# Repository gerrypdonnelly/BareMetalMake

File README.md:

# BareMetalMake
Folder to contain baremetal programming of microcontrollers

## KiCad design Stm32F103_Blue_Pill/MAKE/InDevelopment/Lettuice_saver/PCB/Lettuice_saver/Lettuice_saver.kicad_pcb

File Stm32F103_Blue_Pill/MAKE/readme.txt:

The syscalls.c was created in w3a to accomodate printf
THe linker startup and make files were modified to accomodate the printf through syscalls.c

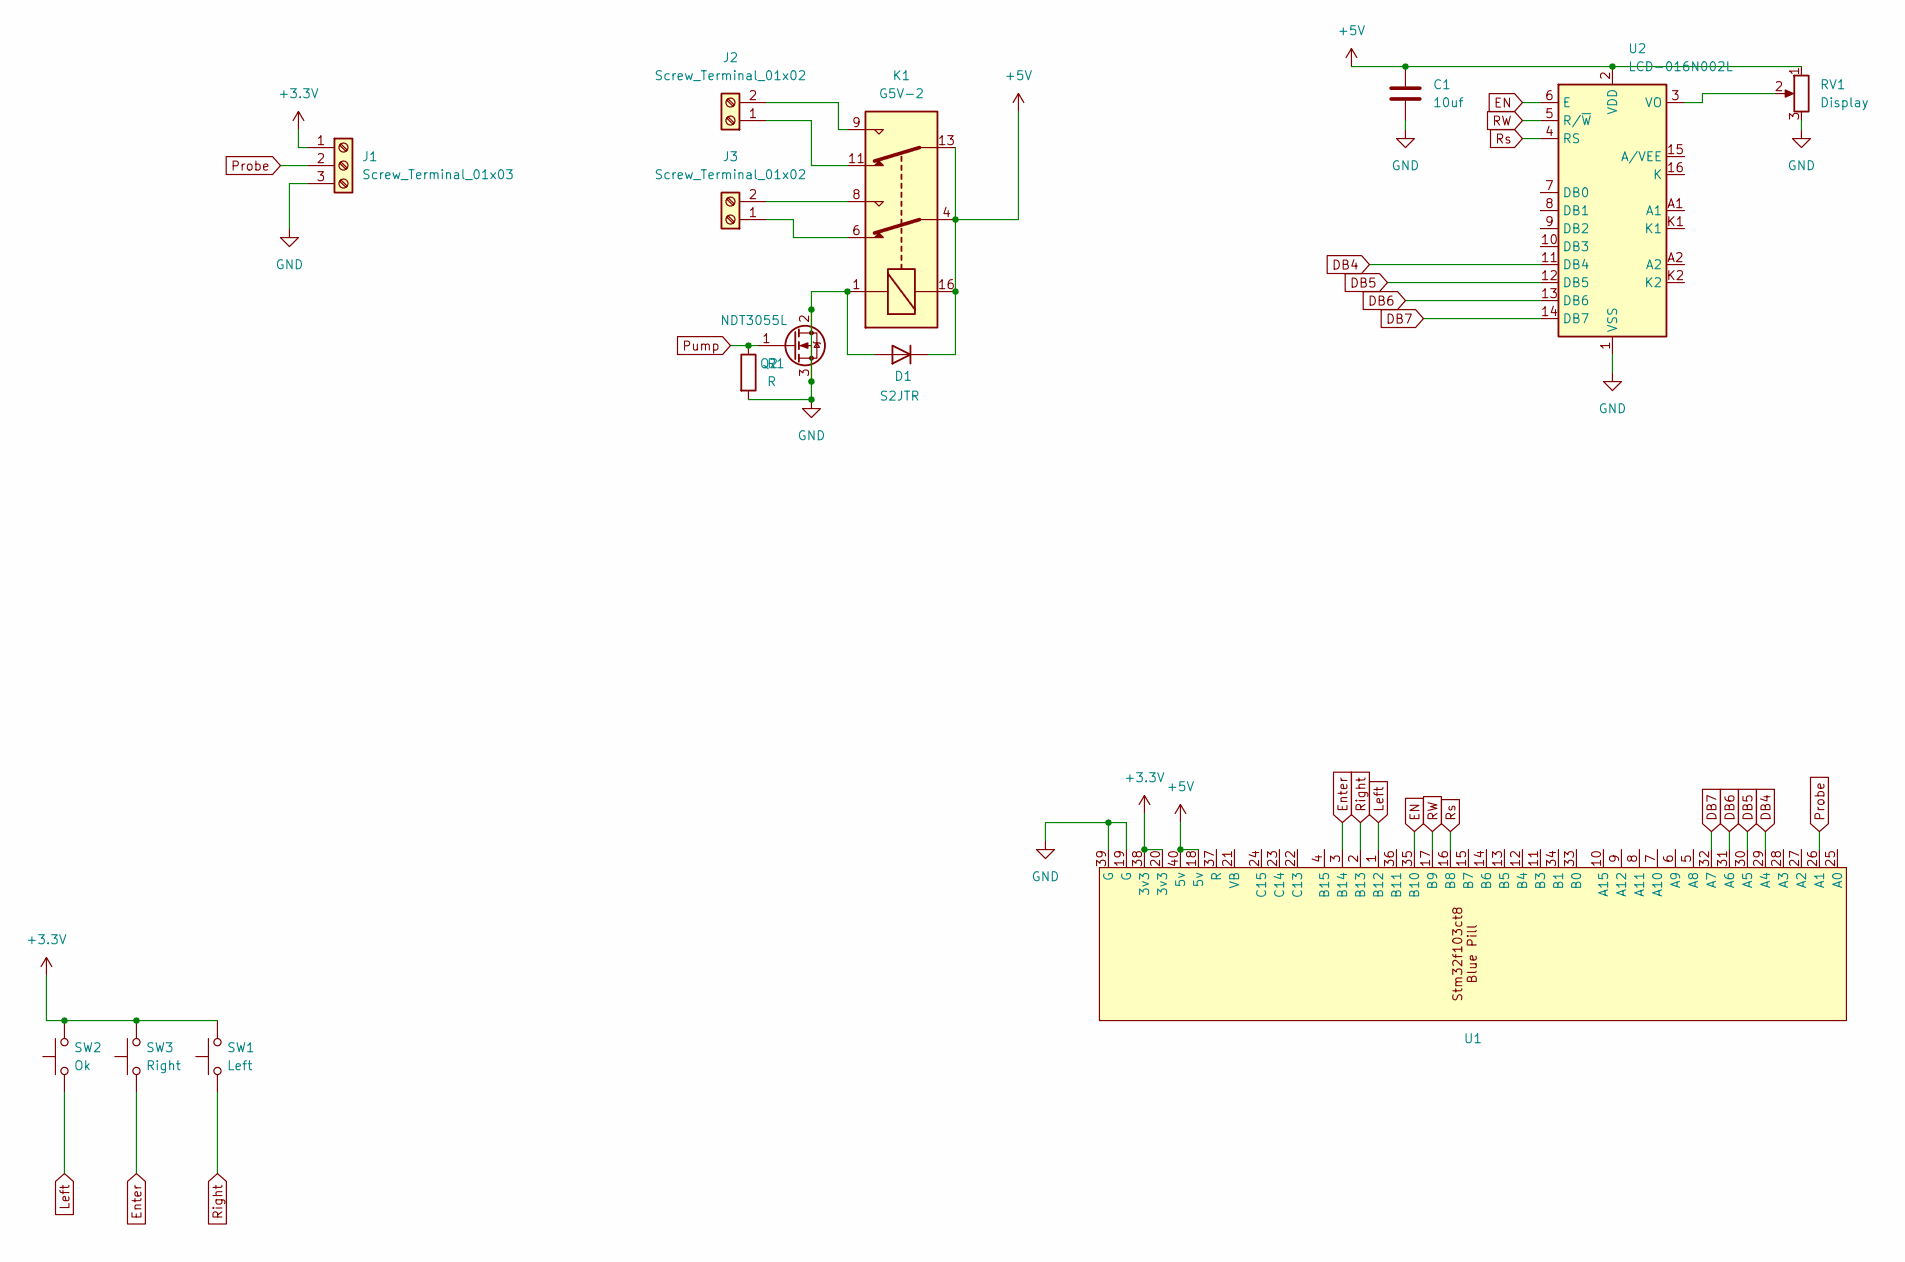
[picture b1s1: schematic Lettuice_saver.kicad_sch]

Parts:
C1: 10uf; C_0402_1005Metric
D1: S2JTR; D_SMB
J1: Screw_Terminal_01x03; TerminalBlock_MaiXu_MX126-5.0-03P_1x03_P5.00mm
J2, J3: Screw_Terminal_01x02; TerminalBlock_MaiXu_MX126-5.0-02P_1x02_P5.00mm
K1: G5V-2; Relay_DPDT_Omron_G5V-2
Q2: NDT3055L; SOT-223-3_TabPin2
R1: R; R_0402_1005Metric
RV1: Display; Potentiometer_Runtron_RM-065_Vertical
SW1: Left; SW_PUSH_6mm
SW2: Ok; SW_PUSH_6mm
SW3: Right; SW_PUSH_6mm
U1: STM32F103 Blue Pill; Blue Pill
U2: LCD-016N002L

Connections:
+3.3V: J1.1, SW1.2, SW2.2, SW3.2, U1.20 (3v3), U1.38 (3v3)
+5V: C1.1, D1.1 (K), K1.4, K1.13, K1.16, RV1.1, U1.18 (5v), U1.40 (5v), U2.2 (VDD)
DB4: U1.29 (A4), U2.11 (DB4)
DB5: U1.30 (A5), U2.12 (DB5)
DB6: U1.31 (A6), U2.13 (DB6)
DB7: U1.32 (A7), U2.14 (DB7)
EN: U1.35 (B10), U2.6 (E)
Enter: SW3.1, U1.3 (B14)
GND: C1.2, D1.2 (A), J1.3, K1.1, Q2.2 (D), Q2.3 (S), R1.2, RV1.3, U1.19 (G), U1.39 (G), U2.1 (VSS)
Left: SW2.1, U1.1 (B12)
unnamed: J2.1, K1.11
unnamed: J2.2, K1.9
unnamed: J3.1, K1.6
unnamed: J3.2, K1.8
unnamed: RV1.2, U2.3 (VO)
Probe: J1.2, U1.26 (A1)
Pump: Q2.1 (G), R1.1
RW: U1.17 (B9), U2.5 (R/~W)
Right: SW1.1, U1.2 (B13)
Rs: U1.16 (B8), U2.4 (RS)

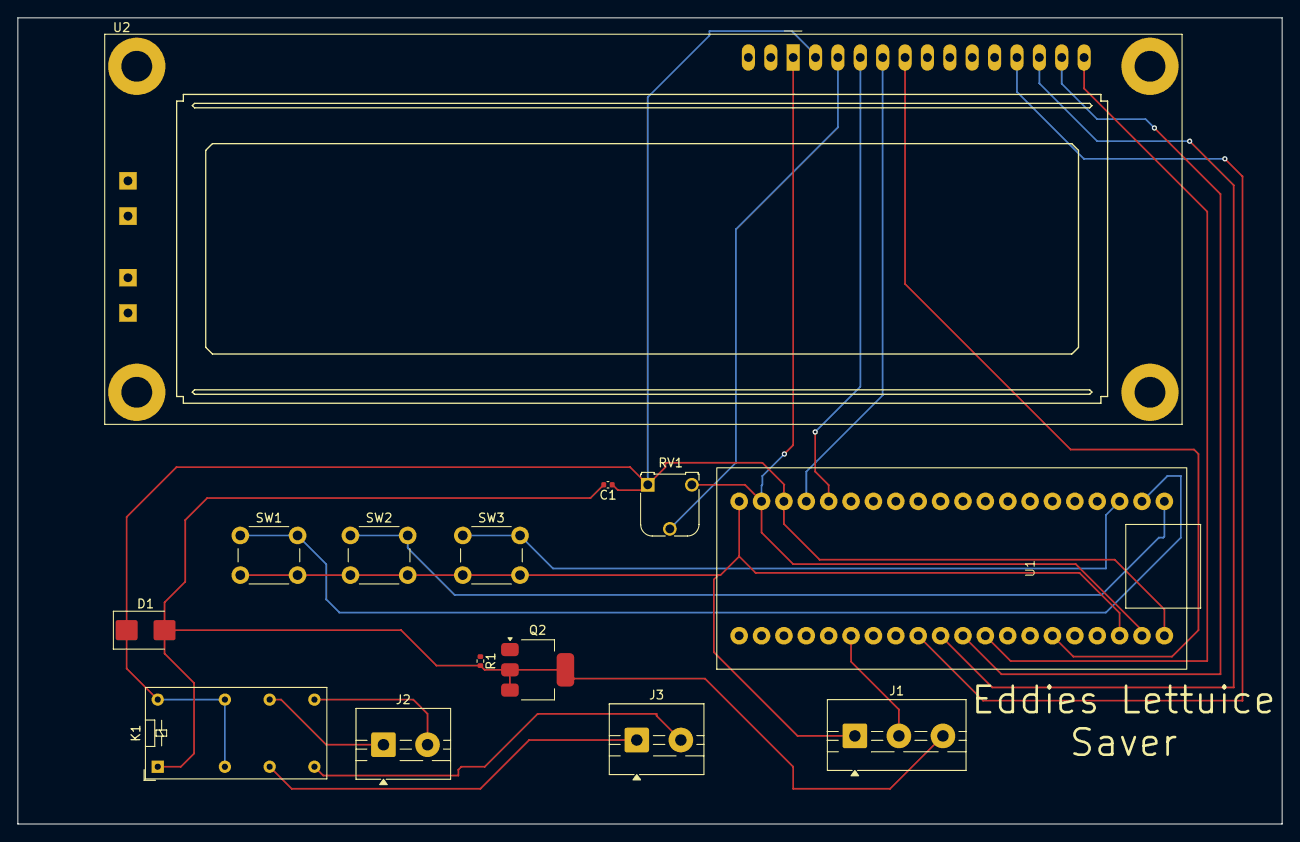
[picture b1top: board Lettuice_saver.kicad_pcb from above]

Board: 2 copper layers, 143.5 x 91.5 mm, 14 parts (0 on the bottom side), 20 nets.

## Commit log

2025-09-12 test
2025-09-12 Added boue pill folder
2025-09-12 Added additional device folders
2025-09-12 added STM32F407 IDE files
2025-09-12 removed built files
2025-09-12 removed compiled files
2025-09-12 updated files
2025-09-12 added gitignore
2025-09-12 removed build files and moved working projects
2025-09-12 made changes to W3_UART_Tx_individual_transmits make file to wor with linux
2025-09-13 made changes to USART w3
2025-09-13 made changes to WDT
2025-09-16 added custom bootloader project
2025-09-16 added custom bootloader folder
2025-09-16 Added bootloader dos from st for stm32f103
2025-09-16 Added bootloader docs and changed W0_blink in MAKE working to generate .hex file
2025-09-16 Added bootloader commands for built in boot loader on stm32f103 blue pill
2025-09-18 added LCD datasheets
2025-09-18 test file added
2025-09-18 removed test.txt
2025-09-18 added test file
2025-09-18 deleted file
2025-11-05 made changes to compile for linux
2025-11-11 added lettuice saver program
2025-11-11 Made corrections to files to work on linux
2025-11-14 made changes to W12 interrupt
2025-11-17 got W12_interrupt to compile and flash
2025-11-17 modified W12 interrupt
2025-11-17 Got W12 interrupt working and moved it to working folder
2025-11-18 changed make to kernel
2025-11-18 changes some non-working progs for test
2025-11-18 removed empty projects
2025-11-18 made changes to WDT_1sec
2025-11-18 Made changes to non working programs
2025-11-18 started on Stm32F411
2025-11-19 made changes to working files
2025-11-19 nothing to add
2025-11-19 made changes to W5_USART
2025-11-19 Added trace
2025-11-22 Fixed W_WDT
2025-11-22 Moved W_WDT to working
2025-11-23 made changes to W5
2025-11-23 made changes to W9
2025-11-24 moved W6 ADC to working
2025-11-25 fixed issue with working W6 ADC single conversion
2025-11-26 made changed to LCD
2025-11-27 Made changes to LCD.c
2025-11-27 changes to LCD.c
2025-11-28 Changes to LCD 8 bit
2025-11-29 Fixed LCD_8bit program
2025-11-30 Changes to LCD fro 4 bit mode
2025-12-01 made changes to LCD 2 line
2025-12-01 made changes to lcd 2 linw
2025-12-01 made changes to LCD 4bit
2025-12-05 Got trace working and moved to working folder
2025-12-05 got two line working with trace and moved to WORKING
2025-12-05 Started working on e-paper module
2025-12-05 made changes to Epaper
2025-12-06 added trace to non working progs
2025-12-06 branched ADC
2025-12-06 continous analog W7 working
2025-12-07 W9 systick timer working and moved to working
2025-12-07 made changes to files to incorperate kernel and removed some directories
2025-12-08 gor W0 interrupt working after replacing startup file with working one
2025-12-08 Made changes to state machine code
2025-12-08 made changes to W11 input compare
2025-12-08 updates to W11
2025-12-08 changed directories
2025-12-08 changed directory structure and removed W
2025-12-08 Added programs for I2C Master and Slave
2025-12-09 Added LED to I2C Master example
2025-12-09 made changes to I2C
2025-12-09 changes to I2C master
2025-12-09 changes to I2CMaster
2025-12-09 Got I2CMaster compiling
2025-12-09 Made changes to I2C Slave
2025-12-10 Made changes to I2C master slave and State machine
2025-12-10 Made changes to I2C LCD
2025-12-11 Added lego and arduino pinout files
2025-12-13 Made changes to LCD I2C
2025-12-14 made changes to I2c Master
2025-12-15 Added watering system menu doc
2025-12-15 menu code
2025-12-15 doc updated
2025-12-16 menu switch statment
2025-12-16 made changes to lettuice saver
2025-12-16 lettuice saver buttons working
2025-12-16 changes to Lettuice saver
2025-12-17 working on lettuice saver button irq
2025-12-17 cleaned up extint in working
2025-12-17 Made changes to lettuice
2025-12-17 changes to lettuics menu
2025-12-17 Changes to lettuice menu
2025-12-17 added code to lettuice menu
2025-12-17 added to lettuice menu
2025-12-18 Added PCB for lettuice saver
2025-12-18 added gbrfiles
2025-12-19 LCD lettuice saver work
2025-12-19 Lettuice saver menu
2025-12-19 Lettuice saver menu flow
2025-12-20 lettuice saver menu updates
2025-12-20 spelling change and branch for menu
2025-12-23 Lettuice saver menu update
2025-12-23 Lettuice saver manu
2025-12-23 Added debounce for buttons
2025-12-23 created debounce for buttons
2025-12-24 water pump control
2025-12-26 Added to auto feature
2026-01-01 Added reading and writing settings to flash
2026-01-01 Added implementation of flash file
2026-01-01 Adding structure for settings
2026-01-01 modification to storing settings in flash
2026-01-09 added more pumps and probes in connection diagram
2026-01-09 Revert "added more pumps and probes in connection diagram"
    This reverts commit bb1b0119f524961f0a8859e8ecd00923546e81bd.
2026-01-09 Revert "modification to storing settings in flash"
    This reverts commit 4ecccb64e59887ff9a36f253ed8a57fc8361e16e.
2026-01-16 cleaned up code
2026-03-05 Tidy up adc.c files
